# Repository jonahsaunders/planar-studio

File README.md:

# Planar Studio

Design planar inductors, transformers, PCB motors, filters and antennas inside
KiCad. Planar Studio reads your board's stack, calculates electrical estimates,
and places the generated copper into the PCB as one undoable operation.

**[Download v1.6.0](https://github.com/jonahsaunders/planar-studio/releases/download/v1.6.0/planar-studio-1.6.0.zip)**
· [Install](#install) · [Guides](#guides) · [Common PCB issues](docs/common-pcb-issues.md) · [Flyback example](#5-w-planar-flyback-example) · [GaN example](#60-w-gan-planar-llc-example) · [CoilTile example](#coiltile-usb-inductive-sensing-example)

## Explore the workspaces

Current application captures. Click a view to open the full-size image.

<table>
<tr>
<td width="50%" valign="top">
<h3>Inductors</h3>

<p>Shape windings, connect layers and route around obstacles.<br><a href="docs/winding-obstacles.md">Winding guide →</a></p>
</td>
<td width="50%" valign="top">
<h3>Transformers</h3>

<p>Build ferrite stacks, compare candidates and verify operating limits.<br><a href="docs/transformer-design.md">Transformer guide →</a></p>
</td>
</tr>
<tr>
<td width="50%" valign="top">
<h3>PCB motors</h3>

<p>Explore rotary, stepper, linear, dual-rotor and planar machines.<br><a href="docs/gallery.md#pcb-motors">See all five motor families →</a></p>
</td>
<td width="50%" valign="top">
<h3>Filters</h3>

<p>Turn LC and microstrip networks into copper and response plots.<br><a href="docs/engineering-models.md#filter-families">Filter models →</a></p>
</td>
</tr>
<tr>
<td width="50%" valign="top">
<h3>Antennas</h3>

<p>Design patches, arrays, directional radiators and NFC loops.<br><a href="docs/gallery.md#antennas">Explore antenna layouts →</a></p>
</td>
<td width="50%" valign="top">
<h3>Design tools</h3>

<p>Inspect fields, optimize geometry and compare measurements.<br><a href="docs/design-tools.md">Design tools guide →</a></p>
</td>
</tr>
</table>

**[Open the full 15-image gallery →](docs/gallery.md)** — obstacle routing,
transformer search, motor families, antenna variants and both interface themes.

Save editable designs, compare calculated responses, and export KiCad boards or
footprints, SVG, DXF, JSON and specification sheets. The **Design tools** panel
adds constrained searches, measurement overlays, tolerance studies and board
checks; see the [tools guide](docs/design-tools.md).

## Install

The **1.6.0 development release** supports KiCad **9.0.1 or newer** on Windows,
macOS and Linux. [Release notes](https://github.com/jonahsaunders/planar-studio/releases/tag/v1.6.0).

1. Download [planar-studio-1.6.0.zip](https://github.com/jonahsaunders/planar-studio/releases/download/v1.6.0/planar-studio-1.6.0.zip) and leave it zipped.
2. In KiCad's main Project Manager, open **Plugin and Content Manager**.
3. Choose **Install from File**, select the ZIP and apply pending changes.
4. Restart KiCad, open the PCB Editor, and launch **Planar Studio** after its
   Python environment finishes setting up.

<details>
<summary>Upgrading or getting a metadata error?</summary>

To upgrade, close Planar Studio and the PCB Editor. In **Plugin and Content
Manager → Installed**, uninstall the old version and apply pending changes
before installing the new ZIP. Saved designs are stored separately; preserve
the settings folder.

Use the installer linked above. GitHub's **Code → Download ZIP** and **Source
code** archives contain the repository, not a PCM installer.

</details>

## 5 W planar flyback example

A10 retains the winding-short repair, increases measured turn gaps to about 0.289 mm, enlarges T1 annular rings and removes tangent secondary-via contacts. Independent geometry, connection-width and full copper/mask Gerber checks protect these changes. Use the A10 package and the [common PCB issues reference](docs/common-pcb-issues.md) when reviewing or editing the design.

An **18–36 V DC to isolated 5 V / 1 A** converter with an LT8302 controller and
transformer windings built into a six-layer PCB. The example includes a KiCad 10
project, schematic, BOM, calculations and single-board manufacturing files for
JLCPCB-managed panelization.

**Unbuilt engineering prototype.** Factory acceptance and electrical, thermal
and magnetic qualification remain open.

[Explore the board and schematic](examples/planar-flyback-5w/README.md)
· [Review package](examples/PS-FLYBACK-5W-A10-review-package.zip)
· [Validation record](examples/planar-flyback-5w/VALIDATION.md)

## 60 W GaN planar LLC example

A **48 V nominal to isolated 12 V / 5 A target** using an integrated GaN half
bridge, silicon synchronous rectifiers and an eight-layer PCB transformer.
The 64 × 56 mm chamfered board has all electronics on top, removable screw-terminal ports,
and the flyback example's exposed-substrate M3 hole geometry on a 55 × 47 mm
pattern. The A10 schematic uses visible local wiring and has no four-way
connections. The accompanying MIT PER and video studies explain the layout decisions. An 82-reference ratings audit records the corrected parts and outstanding electrical limits.

**Unbuilt engineering prototype.** ERC, DRC, connectivity, assembly-file agreement
and a portable rebuild pass. Factory DFM, ferrite installation and electrical,
magnetic and thermal qualification remain open. 60 W is not a measured result.

**Manufacturing audit: do not order the current revision.** The five-board
review found overlapping same-net component lands, incomplete courtyards,
GaN stencil/mask and placement-origin issues, and a factory stack mismatch.
The [audit and cost breakdown](examples/planar-gan-60w/Manufacturing-audit.html)
record required corrections and unconfirmed turnkey operations.

[Explore the native KiCad example](examples/planar-gan-60w/README.md)
· [KiCad package](examples/PS-GAN-60W-A10-KiCad.zip)
· [Layout resource review](examples/planar-gan-60w/DEEP-LAYOUT-REVIEW.md)
· [PER design study](examples/planar-gan-60w/PER-DESIGN-STUDY.md)
· [Validation record](examples/planar-gan-60w/VALIDATION.md)

## CoilTile USB inductive sensing example

A **2 × 2 near-field metal-sensing array** using four printed coils generated by
Planar Studio, an LDC1614 converter and an MCP2221A USB bridge. The A3 schematic
shows one continuous USB → I²C → sensor → LC-tank signal path. The 72 × 90 mm
four-layer PCB reuses the flyback/GaN examples' exposed-substrate M3 edge holes.

Includes editable KiCad 9 files, a Python heatmap and CSV logger, an exact-code
JLCPCB BOM/CPL, Gerbers, and bring-up instructions. No firmware flashing is needed.
**Unbuilt prototype:** native ERC/DRC and connectivity checks pass; physical
sensing range, crosstalk and supplier assembly acceptance remain unverified.

[Explore CoilTile](examples/coil-tile/README.md)
· [Schematic PDF](examples/coil-tile/docs/CoilTile-schematic.pdf)
· [A3 review](examples/coil-tile/docs/A3-CHANGES.md)
· [Assembly handoff](examples/coil-tile/manufacturing/ORDER-NOTES.md)

## Guides

- [Design tools](docs/design-tools.md) — optimization, measurements, tolerances and board checks.
- [Layer setup and loaded transformers](docs/stack-load-antennas.md) — board layers, winding stacks and source/load models.
- [Directional antennas](docs/directional-antennas.md) — Vivaldi, Yagi, log-periodic and bow-tie layouts.
- [Engineering models](docs/engineering-models.md) — equations, reference comparisons, assumptions and limits.
- [Development](docs/development.md) — run without KiCad, build an installer, run checks and capture screenshots.

Calculated performance depends on the selected model. Review its assumptions
and validate the resulting hardware with appropriate simulation, KiCad DRC and
measurements. Transformer loss or thermal results that cannot be calculated are
reported as unknown.

Built on [planar-coil-studio](https://github.com/jonahsaunders/planar-coil-studio).
Released under the [MIT license](LICENSE).

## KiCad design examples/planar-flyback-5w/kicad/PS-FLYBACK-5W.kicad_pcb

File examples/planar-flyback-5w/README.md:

# PS-FLYBACK-5W A10 — winding clearance repairs

An engineering prototype for 18–36 V input and isolated 5 V / 1 A output. [Review report](report.html) · [Validation](VALIDATION.md) · [Manufacturing handoff](manufacturing/START-HERE.md).

**A10 retains the winding-short repair and adds clearance margin.** A7's wide SW landing shorted part of the primary. A8 repaired that landing but retained turn gaps of about 0.191 mm against a 0.200 mm rule. A9 measured approximately 0.240 mm. A10 uses 0.30 mm nominal spacing and measures approximately **0.289 mm** between turns on all four winding layers. The winding stays 0.6 mm wide with 4:2 turns. T1 terminals and attached approaches are updated; both SW necks are retained, and the SEC_A landing retains its 1 mm neck to preserve core-edge clearance. [Repair history](WINDING-CLEARANCE-REVISION.md).

**[Common PCB issues and checks](COMMON-ISSUES.md)** records the causes, why DRC missed them, and how to prevent recurrence. The schematic and PCB drawing layer point to this reference. Independent checks cover external copper, internal turn spacing, physical current paths and matching Gerber winding regions. Regression tests reject the original spacing defect and added/missing copper. [Spacing evidence](evidence/audit/winding-integrity-checks.json) · [A9-to-A10 comparison](evidence/audit/a10-revision-checks.json).

Four secondary via lands increase from 0.90 to 1.00 mm to eliminate tangent contacts. T1 lands increase from 0.60 to 0.70 mm around unchanged 0.30 mm holes, providing 0.20 mm annular rings. The winding size setting increases from 13.6 to 13.9 mm to preserve core-slot clearance. A10 retains the circuit values, component placements, OSP finish, 649 kΩ R1 / C25821, 180 Ω R7, core pair and stack. Resistance, leakage and capacitance estimates are refreshed from the revised winding paths. The estimated magnetizing inductance remains 13.12 µH. Earlier procurement stock figures are historical snapshots. [R1 procurement](PROCUREMENT-REVISION.md) · [Preload derivation](PRELOAD-REVISION.md).

The retained 39 Ω / 2 W snubber screens at **0.638 W**. Its repetitive-pulse capability and measured clamp/thermal behavior remain unqualified. [Snubber review](SNUBBER-REVIEW.md).

## 3D assembly

KiCad render of the saved A10 board. [Underside view](evidence/audit/board-3d-underside.png) · [Side view](evidence/audit/board-3d-side.png) · [STEP model](3d/PS-FLYBACK-5W.step) · [GLB model](3d/PS-FLYBACK-5W.glb). Package/core geometry is nominal; mounting hardware and clip retention include provisional envelopes. See [3D model sources and scope](3D-MODELS.md).

## Layer stack

The cross-section uses the published reference in [stackup.json](stackup.json): **1.609 mm excluding solder mask**, ordered as **1.6 mm nominal**. Layer heights in the illustration are not to scale. This is a modeling reference; the delivered factory construction still needs confirmation.

### Individual copper layers

Each image shows one exported Gerber layer in the same top-view orientation and at the same scale. Read left to right, then down, from L1 to L6; click any image for the full resolution.

| L1 · F.Cu — top | L2 · In1.Cu | L3 · In2.Cu |
| --- | --- | --- |
|  |  |  |
| **L4 · In3.Cu** | **L5 · In4.Cu** | **L6 · B.Cu — bottom** |
|  |  |  |

The primary connects the two-turn windings on **F.Cu and B.Cu in series** for four turns. The two-turn secondary windings on **In1.Cu and In4.Cu connect in parallel**. In2.Cu and In3.Cu carry routing and via pads, with no transformer winding. [Mask, paste, silkscreen and outline views](evidence/audit/gerber-technical-overview.png).

## Schematic

Current A10 schematic exported from KiCad. Open the image to zoom, or download the [native schematic](kicad/PS-FLYBACK-5W.kicad_sch).

## Retained construction

The board is 44 × 94 mm with a 35 × 85 mm mounting pattern and 10 mm copper exclusions around the M3 holes on all six layers. Order nominal 1.6 mm, 1 oz outer / 1 oz inner copper, Specify Stackup: No, OSP finish, and Standard PCBA. The model retains the published default 1.609 mm reference construction; the delivered stack still needs confirmation. [Stack background](STACK-REVISION.md).

The 4:2 planar transformer uses two factory-gapped TDK B66285G0050X187 N87 ELP22 halves and two B66286A2000X000 spring clips. No grinding or adhesive is specified. Install the core pair after PCBA and measure assembled inductance. All 29 footprints have local visible models. [Core installation](manufacturing/CORE-ASSEMBLY.md) · [3D sources](3D-MODELS.md).

## Checks and remaining work

Native ERC/DRC, schematic parity, package/net mapping, winding-spacing and terminal-change containment, mounting/clip clearance, solid fit and manufacturing export checks are recorded in VALIDATION.md. Standard silkscreen text is at least 1.0 mm high with 0.15 mm strokes and a 0.15 mm clearance rule.

The placement check covers 24 components, 50 saved exact-part catalog pad centers, four R1/R6 manufacturer land centers and two R7 same-series reference centers, with 15 rejected incorrect rotations/origins. Replacement R1/R6/R7 catalog geometry was unavailable; confirm these centered nonpolar placements in the fresh factory preview. [Placement review](manufacturing/PLACEMENT-REVIEW.md).

This remains an unbuilt prototype. Supplier acceptance of the stack, filled/capped vias, panel, Standard-PCBA reflow and connector process is open. Bench qualification must establish clamp and RFB waveforms, snubber pulse/thermal behavior, regulation, magnetics, startup/fault behavior and clip retention. The A10 repair has been checked in CAD; hardware qualification remains open.

## Rebuild

Run `scripts/rebuild.py --kicad-cli <KiCad-10-cli> --kicad-python <KiCad-Python-or-wrapper> --cadquery-python <Python-with-CadQuery-PyGerber-Pillow> --geometry-python <Python-with-Shapely-2.2-and-PyGerber-2.4.3>`. If Shapely is available in the CadQuery environment, omit `--geometry-python`. Node and Sharp rasterize the schematic; use `--node` and `--sharp-module` when they are not on the default paths. The default uses the saved A10 winding/core source; `--regenerate-magnetics` regenerates it from the repository engine and `winding-clearance.json`. The A10 comparison bounds winding, terminal, approach and four via-land changes. Nonzero connection-width, mask-clearance and annular-ring checks run alongside independent winding and complete copper/mask Gerber comparisons. The build refreshes native files, checks, manufacturing data, views and the A10 review ZIP.

The current A10 evidence is enumerated in VALIDATION.md. Earlier A1–A9 reports and images are historical context, not fresh proof for this board.

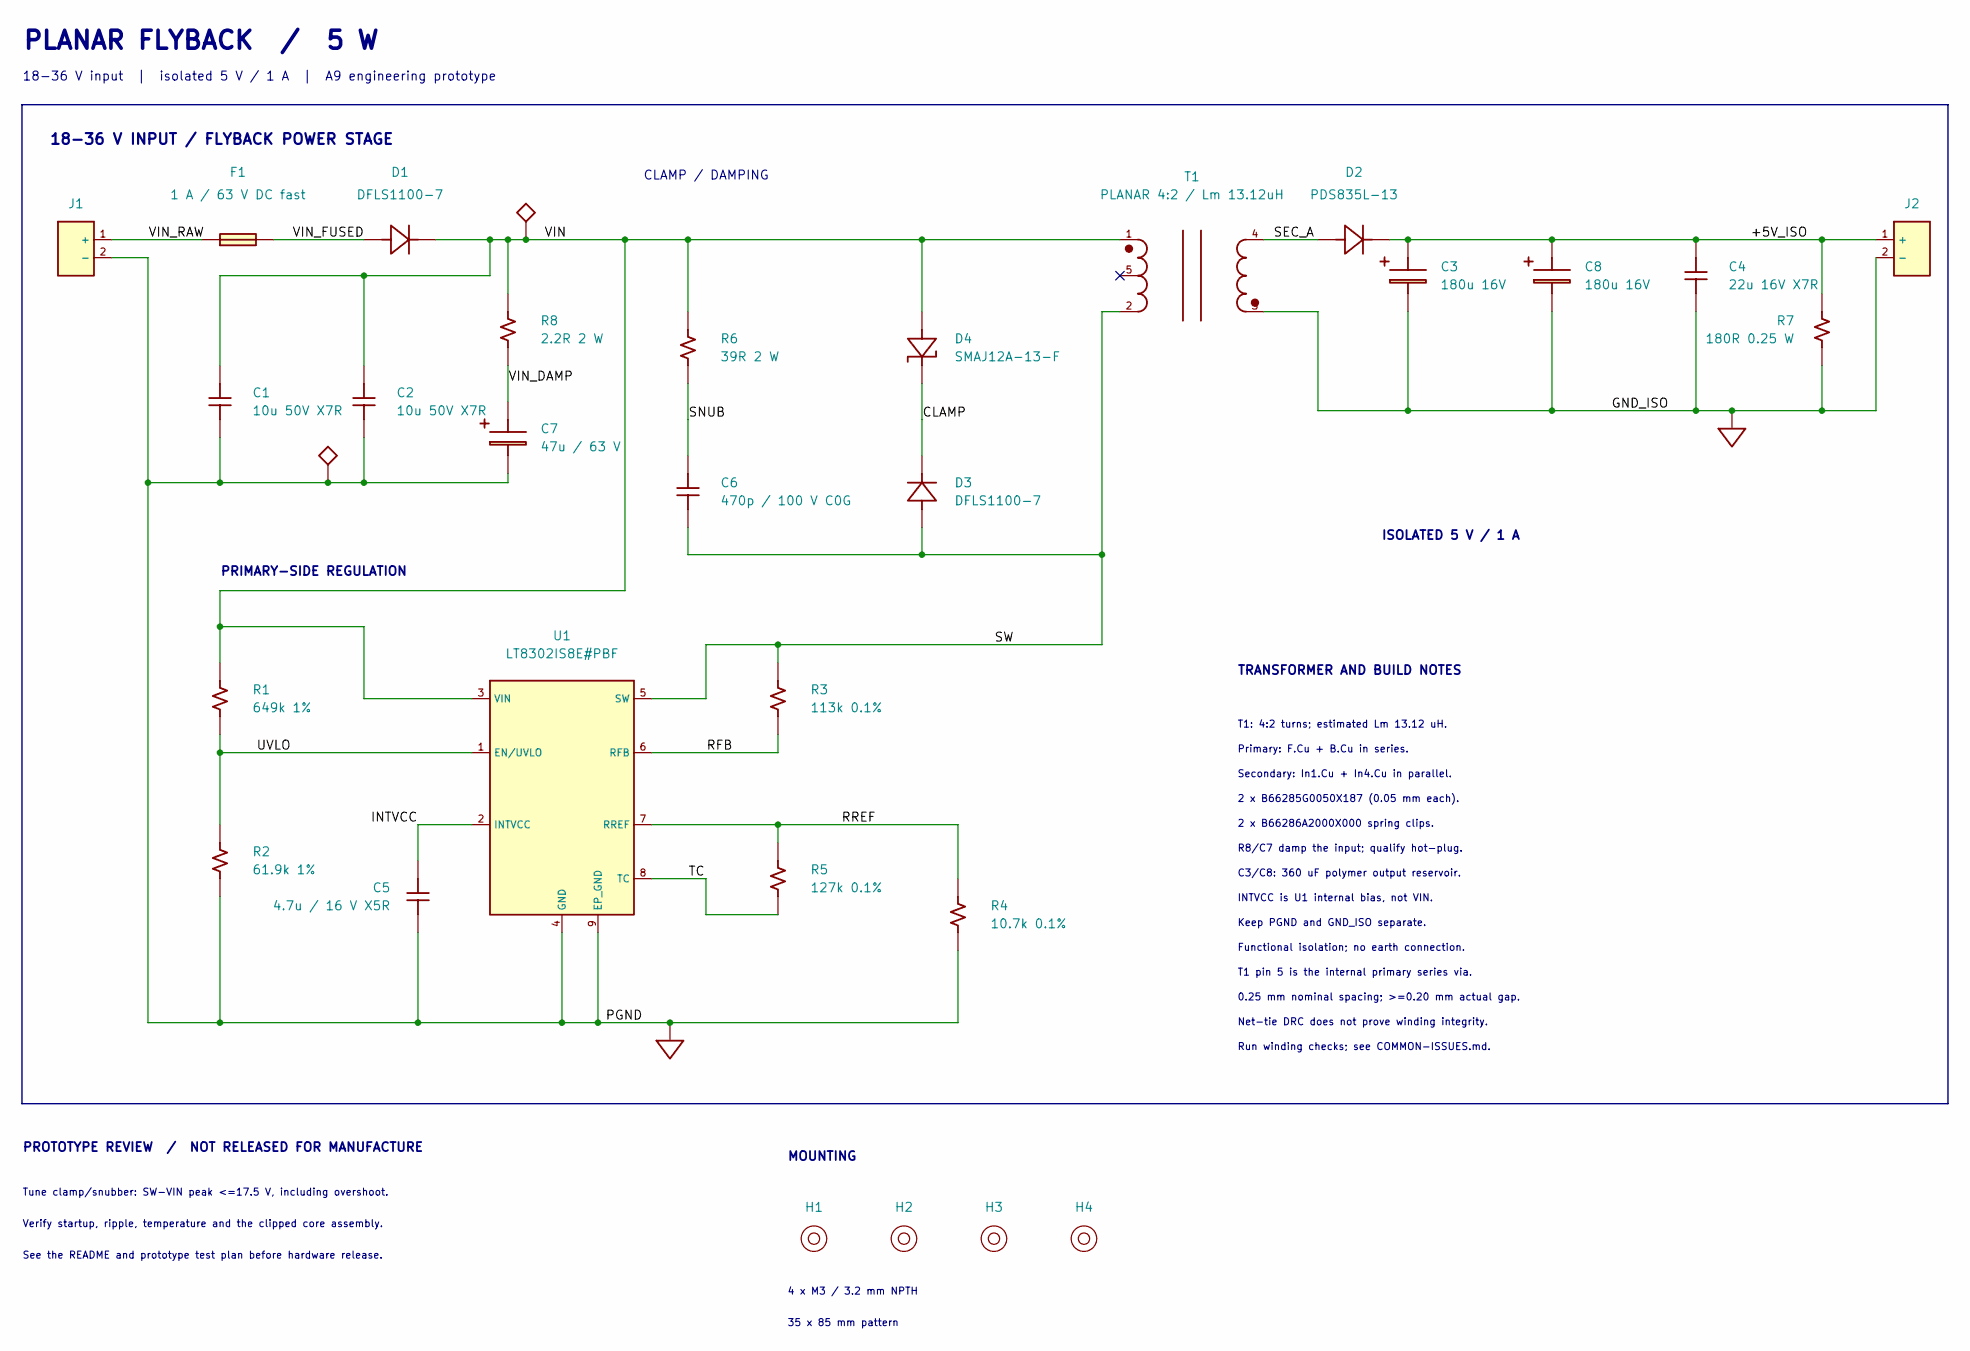
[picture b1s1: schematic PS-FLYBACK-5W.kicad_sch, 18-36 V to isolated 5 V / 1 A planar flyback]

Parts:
C1, C2: 10u 50V X7R; C_1210_3225Metric; MPN CL32B106KBJNNNE; LCSC C138687
C3, C8: 180u 16V; CP_Panasonic_C6; MPN 16SVPF180M; LCSC C136277
C4: 22u 16V X7R; C_1210_3225Metric; MPN CL32B226KOJNNNE; LCSC C55530
C5: 4.7u / 16 V X5R; C_0603_1608Metric; MPN GRM188R61C475KE11D; LCSC C77045
C6: 470p / 100 V C0G; C_0805_2012Metric; MPN CC0805JRNPO0BN471; LCSC C513677
C7: 47u / 63 V; CP_Elec_8x10.5; MPN EEHZC1J470P; LCSC C454353
D1, D3: DFLS1100-7; D_PowerDI-123; MPN DFLS1100-7; LCSC C107674
D2: PDS835L-13; D_PowerDI-5; MPN PDS835L-13; LCSC C444972
D4: SMAJ12A-13-F; D_SMA; MPN SMAJ12A-13-F; LCSC C134947
F1: 1 A / 63 V DC fast; Fuse_Bourns_SF1206F; MPN SF-1206F100-2; LCSC C3164649
H1, H2, H3, H4: M3 / 3.2 mm NPTH; MountingHole_3.2mm_M3_ExposedSubstrate_Edge
J1: 18-36 V DC; Terminal_KF301_2P_5.00; MPN KF301-5.0-2P; LCSC C474881
J2: 5 V / 1 A isolated; Terminal_KF301_2P_5.00; MPN KF301-5.0-2P; LCSC C474881
R1: 649k 1%; R_0603_1608Metric; MPN 0603WAF6493T5E; LCSC C25821
R2: 61.9k 1%; R_0603_1608Metric; MPN RC0603FR-0761K9L; LCSC C137696
R3: 113k 0.1%; R_0603_1608Metric; MPN RT0603BRD07113KL; LCSC C705718
R4: 10.7k 0.1%; R_0603_1608Metric; MPN RT0603BRD0710K7L; LCSC C861078
R5: 127k 0.1%; R_0603_1608Metric; MPN RT0603BRD07127KL; LCSC C705722
R6: 39R 2 W; R_EverOhms_CRH2512; MPN CRH2512F39R0E04Z; LCSC C175263
R7: 180R 0.25 W; R_1206_3216Metric; MPN RC1206FR-07180RL; LCSC C137380
R8: 2.2R 2 W; R_Bourns_CRM2512; MPN CRM2512-JW-2R2ELF; LCSC C840598
T1: PLANAR 4:2 / Lm 13.12uH; Planar_EELP22_4T_2T; MPN PS-MAG-002 A2
U1: LT8302IS8E#PBF; SOIC8_EP_LT_S8E; MPN LT8302IS8E#PBF; LCSC C673679

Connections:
/+5V_ISO: C3.1, C4.1, C8.1, D2.1 (K), J2.1 (+), R7.1
/CLAMP: D3.1 (K), D4.1 (K)
/GND_ISO: C3.2, C4.2, C8.2, J2.2 (-), R7.2, T1.3 (S_DOT)
/INTVCC: C5.1, U1.2 (INTVCC)
/PGND: C1.2, C2.2, C5.2, C7.2, J1.2 (-), R2.2, R4.2, U1.4 (GND), U1.9 (EP_GND)
/RFB: R3.2, U1.6 (RFB)
/RREF: R4.1, R5.2, U1.7 (RREF)
/SEC_A: D2.2 (A), T1.4 (S_END)
/SNUB: C6.1, R6.2
/SW: C6.2, D3.2 (A), R3.1, T1.2 (P_END), U1.5 (SW)
/TC: R5.1, U1.8 (TC)
/UVLO: R1.2, R2.1, U1.1 (EN/UVLO)
/VIN: C1.1, C2.1, D1.1 (K), D4.2 (A), R1.1, R6.1, R8.1, T1.1 (P_DOT), U1.3 (VIN)
/VIN_DAMP: C7.1, R8.2
/VIN_FUSED: D1.2 (A), F1.2
/VIN_RAW: F1.1, J1.1 (+)

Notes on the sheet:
PRIMARY-SIDE REGULATION
CLAMP / DAMPING
ISOLATED 5 V / 1 A
TRANSFORMER AND BUILD NOTES
T1: 4:2 turns; estimated Lm 13.12 uH.
Primary: F.Cu + B.Cu in series.
Secondary: In1.Cu + In4.Cu in parallel.
2 x B66285G0050X187 (0.05 mm each).
2 x B66286A2000X000 spring clips.
R8/C7 damp the input; qualify hot-plug.
C3/C8: 360 uF polymer output reservoir.
INTVCC is U1 internal bias, not VIN.
Keep PGND and GND_ISO separate.
Functional isolation; no earth connection.
T1 pin 5 is the internal primary series via.
0.25 mm nominal spacing; >=0.20 mm actual gap.
Net-tie DRC does not prove winding integrity.
Run winding checks; see COMMON-ISSUES.md.
PLANAR FLYBACK / 5 W
18-36 V input | isolated 5 V / 1 A | A9 engineering prototype
18-36 V INPUT / FLYBACK POWER STAGE
PROTOTYPE REVIEW / NOT RELEASED FOR MANUFACTURE
Tune clamp/snubber: SW-VIN peak <=17.5 V, including overshoot.
Verify startup, ripple, temperature and the clipped core assembly.
See the README and prototype test plan before hardware release.
MOUNTING
4 x M3 / 3.2 mm NPTH
35 x 85 mm pattern

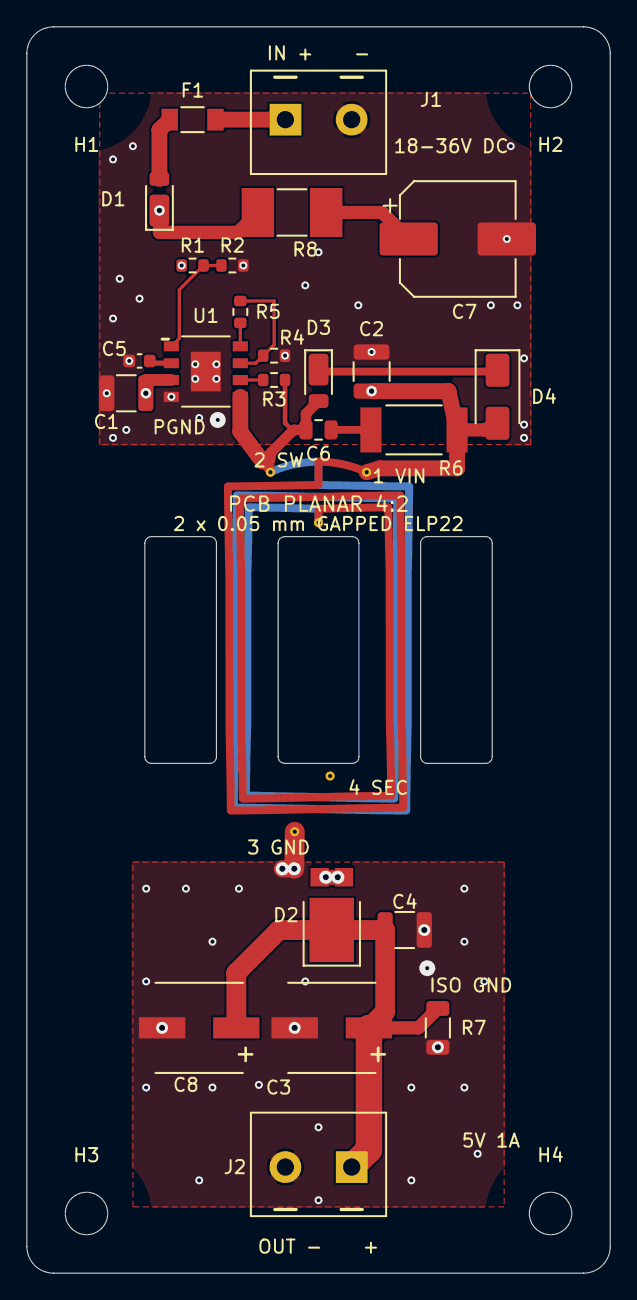
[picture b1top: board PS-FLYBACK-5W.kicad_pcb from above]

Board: 6 copper layers, 44.0 x 94.0 mm, 29 parts (0 on the bottom side), 16 nets.

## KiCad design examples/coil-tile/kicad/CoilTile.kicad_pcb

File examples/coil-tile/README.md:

# CoilTile A3 — a four-pixel metal-sensing PCB

**Prototype design, not yet fabricated or tested on hardware.** Four printed
24 mm coils sense changes in nearby conductive targets. An LDC1614 measures
their resonant frequencies; an MCP2221A connects them to a USB desktop heatmap.
This is a near-field inductive array, not radar or an RF direction-finding array.

A3 keeps the continuous USB-C → ESD → USB/I²C bridge → sensor → LC-tank
schematic, with smaller symbols, tighter spacing and clear service notes.
The PCB has shorter I²C/CC1 routes, labeled service pads and a closer sensor
bypass capacitor. All four mounting holes retain the American Embedded
exposed-substrate footprint used by the flyback and GaN examples.
See [A3 changes and measured routing improvements](docs/A3-CHANGES.md).

[View the schematic PDF](docs/CoilTile-schematic.pdf) · [Angled 3D view](evidence/assembled-board-perspective.png) · [3D model details](docs/3D-MODELS.md).

## What is included

| Folder | Contents |
|---|---|
| `kicad/` | Editable KiCad 9 project, schematic, routed PCB, local symbols and footprints |
| `docs/CoilTile-schematic.pdf` | Readable one-sheet A3 schematic |
| `manufacturing/` | Fabrication ZIP, JLCPCB BOM and placement CSV, order notes |
| `software/` | USB driver, 2×2 heatmap, baseline calibration, CSV logger, explicit demo mode |
| `planar-studio/` | Coil configuration, generated artwork, geometry and estimated model |
| `evidence/` | Native ERC/DRC, netlist, layer/Gerber previews, assembly checks and software tests |
| `scripts/` | Source generators and release/export checks |

Start by opening `kicad/CoilTile.kicad_pro`, then read `docs/BRINGUP.md` and
`manufacturing/ORDER-NOTES.md`. The board is fully routed. There is no firmware
image or programming service to arrange: MCP2221A uses factory USB firmware.
The Python application runs on the computer, not the PCB.

## Design

72 × 90 mm, 1.6 mm FR-4, four copper layers, 20 assembled components on the top.
Four 3.2 mm mounting holes have 6.4 mm exposed-substrate mask openings and 10 mm
copper exclusion circles, with mask extensions toward the nearest side edge.
They retain the 64 × 82 mm mounting pattern and take nylon hardware. The analog converter sits at the
center; USB, ESD protection and a 3.3 V linear regulator occupy the bottom strip.

The four single-layer coils use 16 turns of 0.20 mm trace / 0.20 mm spacing.
Planar Studio estimates about 5.51 µH per coil. A 220 pF C0G capacitor gives an
ideal resonance near 4.57 MHz; routing, materials, targets and mutual coupling
will shift that. Inner coil terminals return on the back. Ground and power
planes are kept outside the sensing disks. Coils remain covered by soldermask.

Four layers were chosen for dependable power and return paths around the USB
bridge and sensor. This costs more bare-board area than two layers, but avoids
a fragile two-layer escape layout. The board uses standard through vias and
no via-in-pad fabrication, blind vias, or solder-mask-defined fine-pitch tricks.

The heatmap shows relative frequency changes. It does not claim distance,
material identity, four independent spatial pixels, or a validated detection
range. Start experiments with coins/washers a few millimeters away. Backside
metal also affects it. Use a plastic stand and keep a laptop chassis away.

## Cost and assembly

Planning allowance: **roughly US$85–120 for five assembled boards before
shipping/tax**, not a JLCPCB quotation. The two main ICs account for most of the
parts cost. Small-order setup, extended-component fees, stencil, QFN inspection,
connector soldering and wastage can outweigh the bare PCB price. Actual service
eligibility, stock and all fees must be checked in JLCPCB's order review.

All purchased parts have exact LCSC codes in the native schematic and BOM.
The coils, test pads and mounting holes are fabricated features, not BOM parts.
Request complete top-side assembly including the USB connector's shell stakes.
No order has been placed. A cable and nylon standoffs are not included in the BOM.

## Verification and remaining work

KiCad 9.0.9 ERC and DRC report **zero violations**, zero unrouted connections,
and zero schematic parity issues. BOM and CPL both contain exactly the same
20 assembly references. Gerber copper/mask/paste/silk/outline files were parsed
and rendered separately from the native PCB. Schematic PDF and layer views
were visually reviewed. Seven mocked driver tests pass; headless demo/CSV runs.

These checks cannot verify oscillation amplitude, USB signal integrity, sensor
noise, usable range, crosstalk or assembly yield. The first batch is for bring-up
and characterization. The GUI/USB path still needs a real-machine/device run.
See `docs/VALIDATION.md` for the exact boundaries of the verification.

## References used

Built using the [KiStack](https://github.com/American-Embedded/kistack) schematic,
PCB, BOM and export workflows, and
[Planar Studio](https://github.com/jonahsaunders/planar-studio)'s actual inductor
engine. Reviewed its planar-flyback example generators, schematic and layout
audits for portable libraries, winding artwork/net-tie handling, readable
schematics and release checks. Those examples are not proof this sensor works.

Commit pins, datasheet links, licenses and design choices are in
`docs/REFERENCES.md`. See `docs/REBUILD.md` before running the generators: they
overwrite the native design files, so edit in KiCad or regenerate deliberately.

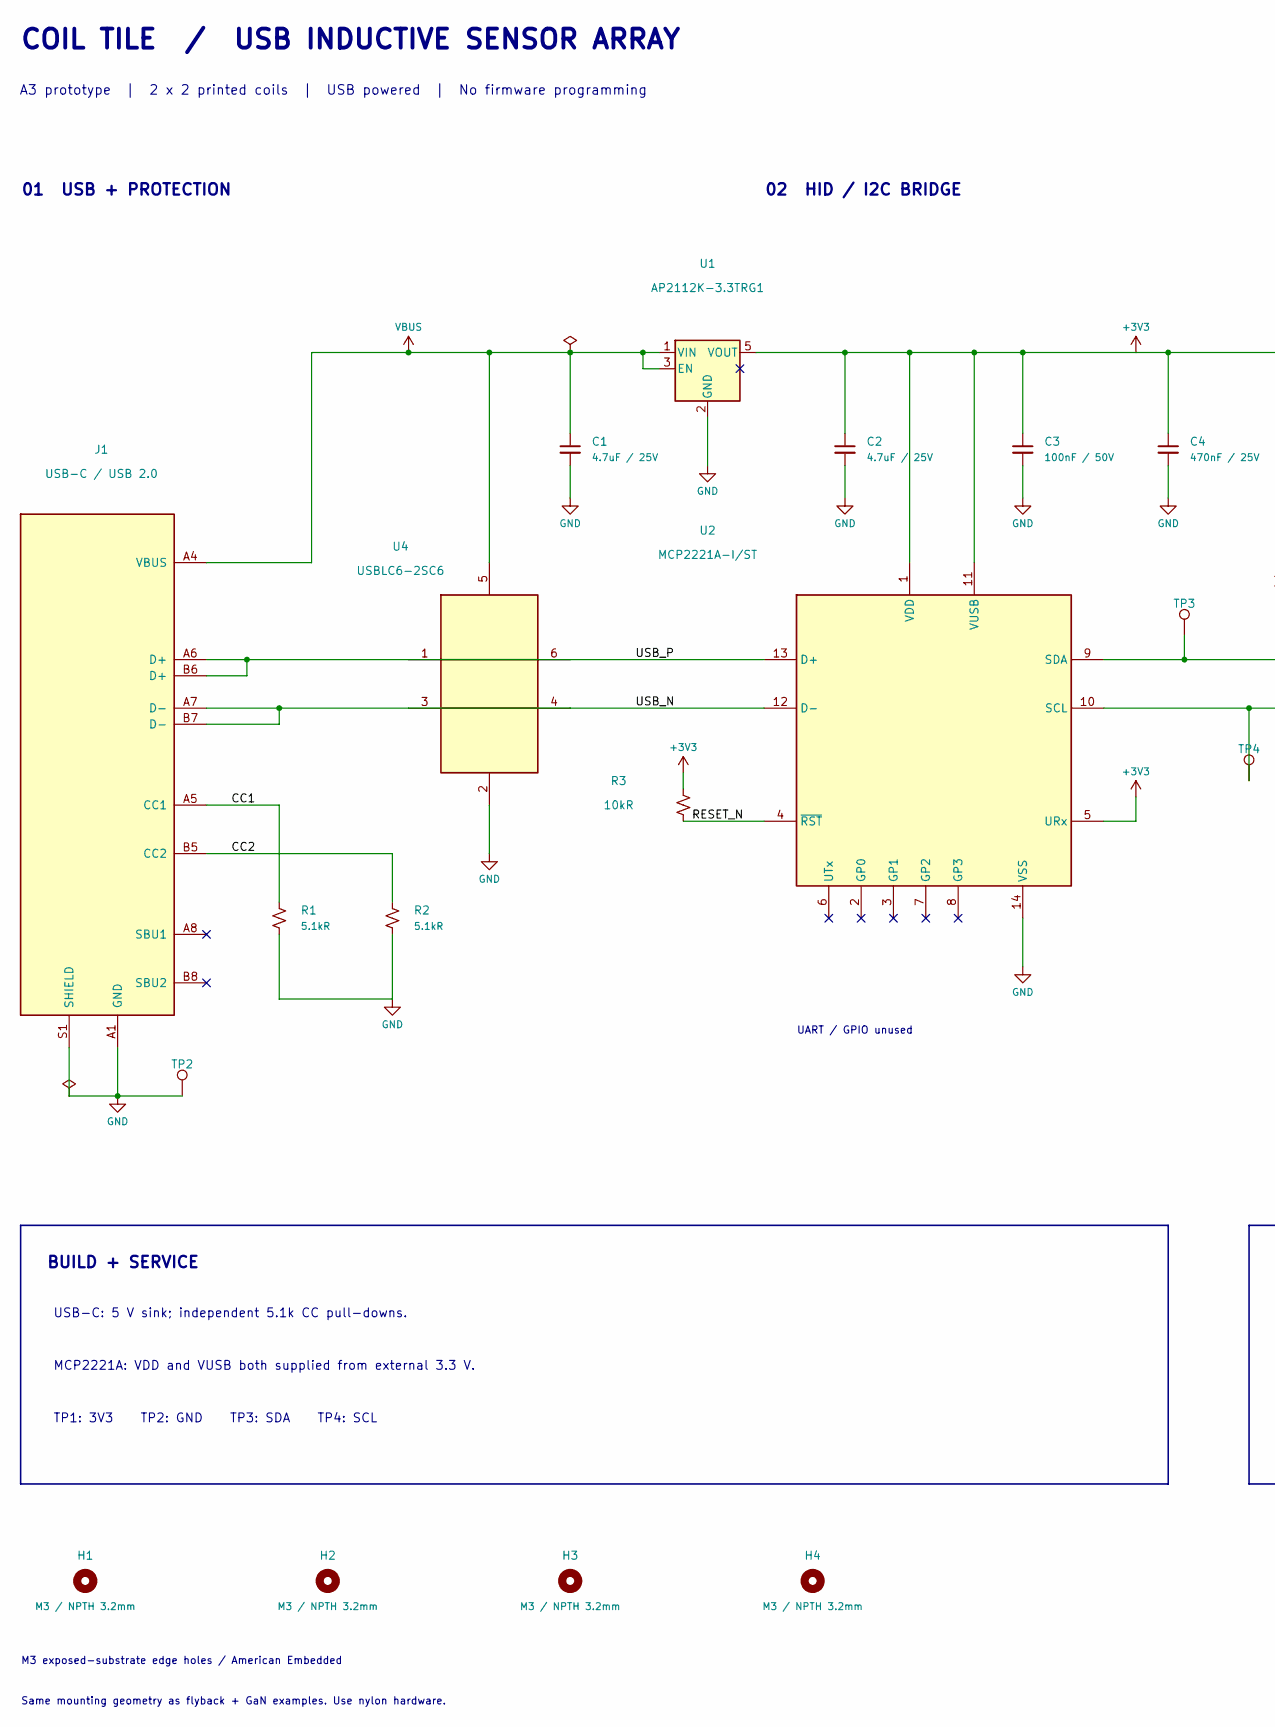
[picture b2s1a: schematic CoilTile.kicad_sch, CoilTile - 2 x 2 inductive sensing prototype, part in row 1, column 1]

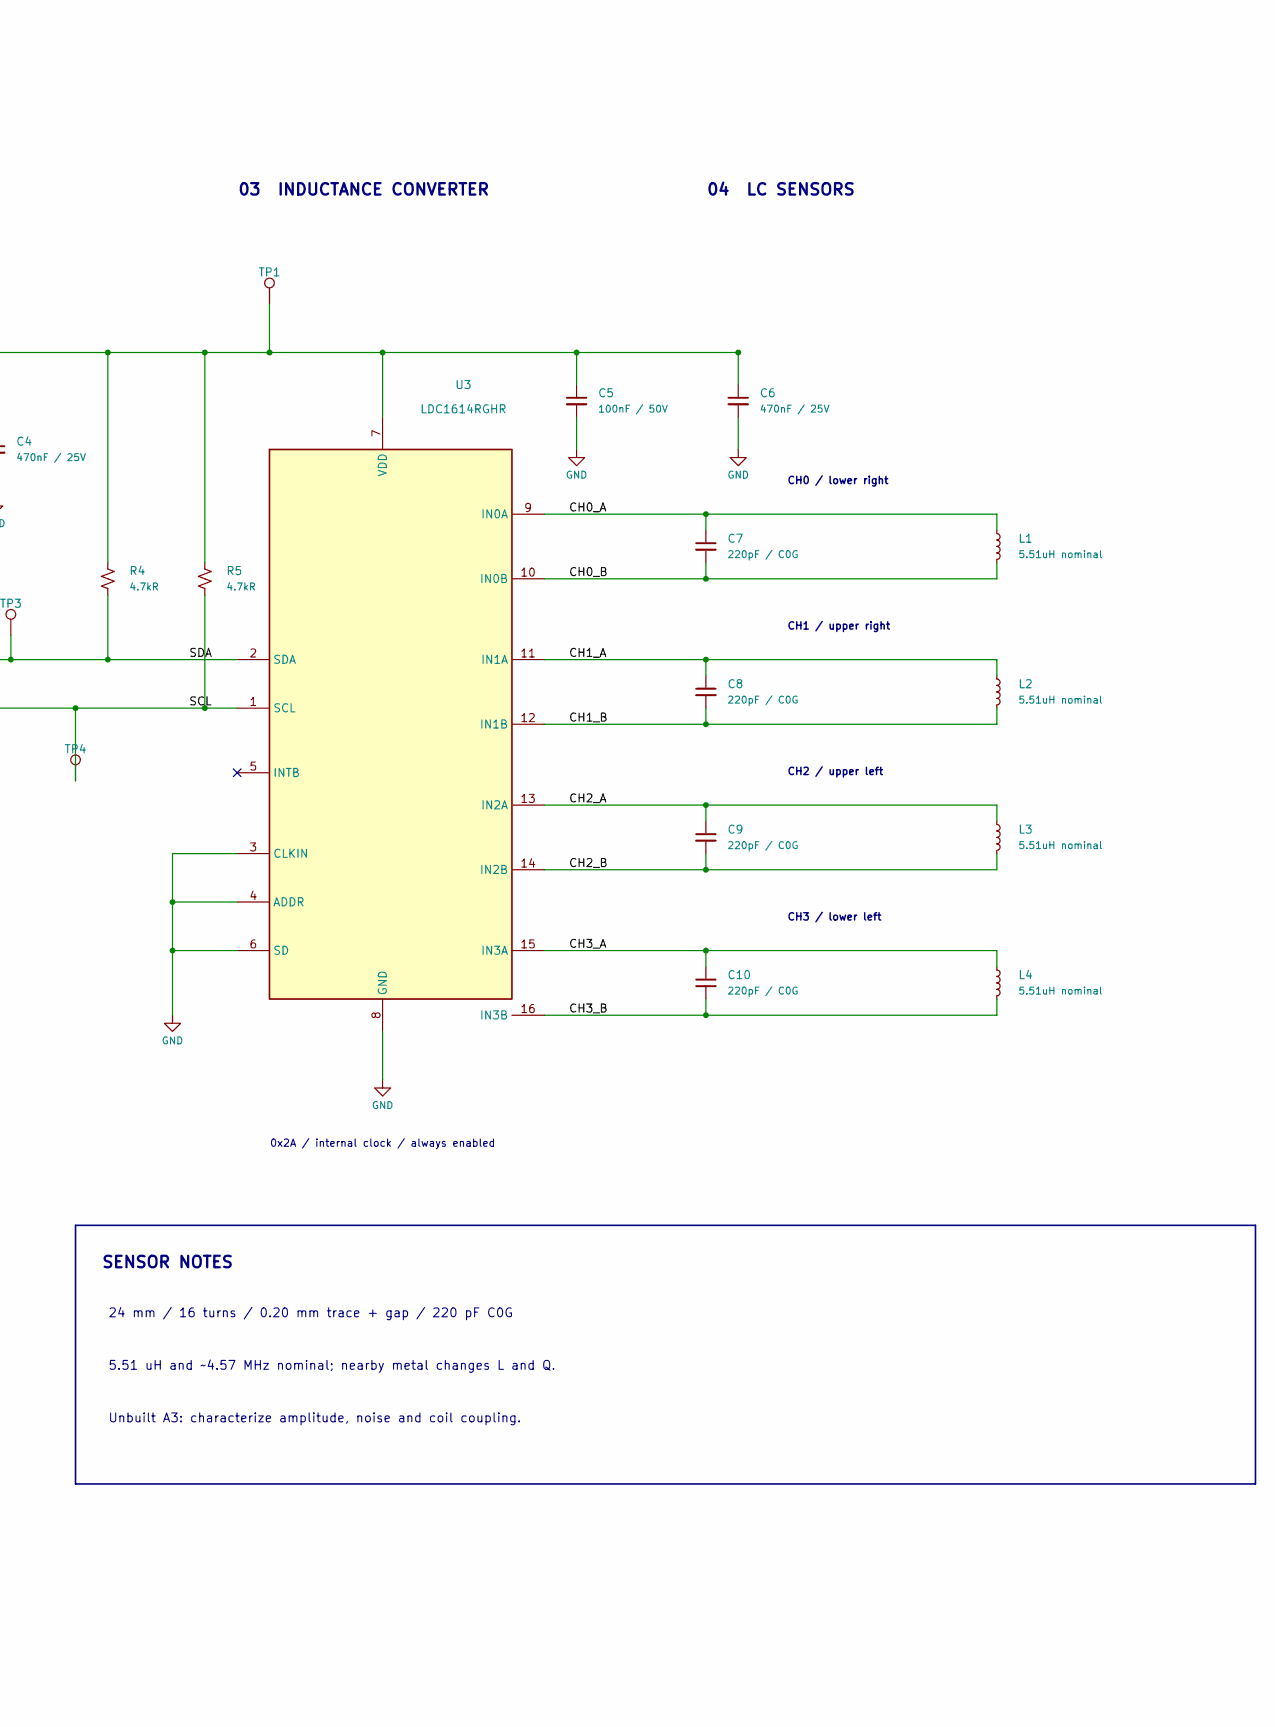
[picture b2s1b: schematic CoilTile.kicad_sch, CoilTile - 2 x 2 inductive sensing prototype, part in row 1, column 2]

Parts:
C1, C2: 4.7uF / 25V; C_0805_2012Metric; MPN CC0805KKX7R8BB475; LCSC C354262
C3, C5: 100nF / 50V; C_0603_1608Metric; MPN CC0603KRX7R9BB104; LCSC C14663
C4, C6: 470nF / 25V; C_0603_1608Metric; MPN CL10B474KA8NNNC; LCSC C1623
C7, C8, C9, C10: 220pF / C0G; C_0603_1608Metric; MPN 0603CG221J500NT; LCSC C156398
H1, H2, H3, H4: M3 / NPTH 3.2mm; MountingHole_3.2mm_M3_ExposedSubstrate_Edge
J1: USB-C / USB 2.0; USB_C_Receptacle_HRO_TYPE-C-31-M-12; MPN TYPE-C-31-M-12; LCSC C165948
L1, L2, L3, L4: 5.51uH nominal; Planar_24mm_16T; MPN PCB winding / not fitted
R1, R2: 5.1kR; R_0603_1608Metric; MPN 0603WAF5101T5E; LCSC C23186
R3: 10kR; R_0603_1608Metric; MPN 0603WAF1002T5E; LCSC C25804
R4, R5: 4.7kR; R_0603_1608Metric; MPN 0603WAF4701T5E; LCSC C23162
TP1: +3V3; TestPoint_Pad_D1.0mm
TP2: GND; TestPoint_Pad_D1.0mm
TP3: SDA; TestPoint_Pad_D1.0mm
TP4: SCL; TestPoint_Pad_D1.0mm
U1: AP2112K-3.3TRG1; SOT-23-5; MPN AP2112K-3.3TRG1; LCSC C51118
U2: MCP2221A-I/ST; TSSOP-14_4.4x5mm_P0.65mm; MPN MCP2221A-I/ST; LCSC C130462
U3: LDC1614RGHR; WQFN-16-1EP_4x4mm_P0.5mm_EP2.6x2.6mm; MPN LDC1614RGHR; LCSC C968448
U4: USBLC6-2SC6; SOT-23-6; MPN USBLC6-2SC6; LCSC C7519

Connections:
+3V3: C2.1, C3.1, C4.1, C5.1, C6.1, R3.1, R4.1, R5.1, TP1.1, U1.5 (VOUT), U2.1 (VDD), U2.5 (URx), U2.11 (VUSB), U3.7 (VDD)
/CC1: J1.A5 (CC1), R1.1
/CC2: J1.B5 (CC2), R2.1
/CH0_A: C7.1, L1.1, U3.9 (IN0A)
/CH0_B: C7.2, L1.2, U3.10 (IN0B)
/CH1_A: C8.1, L2.1, U3.11 (IN1A)
/CH1_B: C8.2, L2.2, U3.12 (IN1B)
/CH2_A: C9.1, L3.1, U3.13 (IN2A)
/CH2_B: C9.2, L3.2, U3.14 (IN2B)
/CH3_A: C10.1, L4.1, U3.15 (IN3A)
/CH3_B: C10.2, L4.2, U3.16 (IN3B)
/RESET_N: R3.2, U2.4 (~RST)
/SCL: R5.2, TP4.1, U2.10 (SCL), U3.1 (SCL)
/SDA: R4.2, TP3.1, U2.9 (SDA), U3.2 (SDA)
/USB_N: J1.A7 (D-), J1.B7 (D-), U2.12 (D-), U4.3 (I/O2), U4.4 (I/O2)
/USB_P: J1.A6 (D+), J1.B6 (D+), U2.13 (D+), U4.1 (I/O1), U4.6 (I/O1)
GND: C1.2, C2.2, C3.2, C4.2, C5.2, C6.2, J1.A1 (GND), J1.A12 (GND), J1.B1 (GND), J1.B12 (GND), J1.S1 (SHIELD), R1.2, R2.2, TP2.1, U1.2 (GND), U2.14 (VSS), U3.3 (CLKIN), U3.4 (ADDR), U3.6 (SD), U3.8 (GND), U3.17 (GND), U4.2 (GND)
VBUS: C1.1, J1.A4 (VBUS), J1.A9 (VBUS), J1.B4 (VBUS), J1.B9 (VBUS), U1.1 (VIN), U1.3 (EN), U4.5 (VBUS)

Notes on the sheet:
COIL TILE / USB INDUCTIVE SENSOR ARRAY
A3 prototype | 2 x 2 printed coils | USB powered | No firmware programming
01 USB + PROTECTION
02 HID / I2C BRIDGE
03 INDUCTANCE CONVERTER
04 LC SENSORS
UART / GPIO unused
0x2A / internal clock / always enabled
CH0 / lower right
CH1 / upper right
CH2 / upper left
CH3 / lower left
BUILD + SERVICE
USB-C: 5 V sink; independent 5.1k CC pull-downs.
MCP2221A: VDD and VUSB both supplied from external 3.3 V.
TP1: 3V3 TP2: GND TP3: SDA TP4: SCL
SENSOR NOTES
24 mm / 16 turns / 0.20 mm trace + gap / 220 pF C0G
5.51 uH and ~4.57 MHz nominal; nearby metal changes L and Q.
Unbuilt A3: characterize amplitude, noise and coil coupling.
M3 exposed-substrate edge holes / American Embedded
Same mounting geometry as flyback + GaN examples. Use nylon hardware.

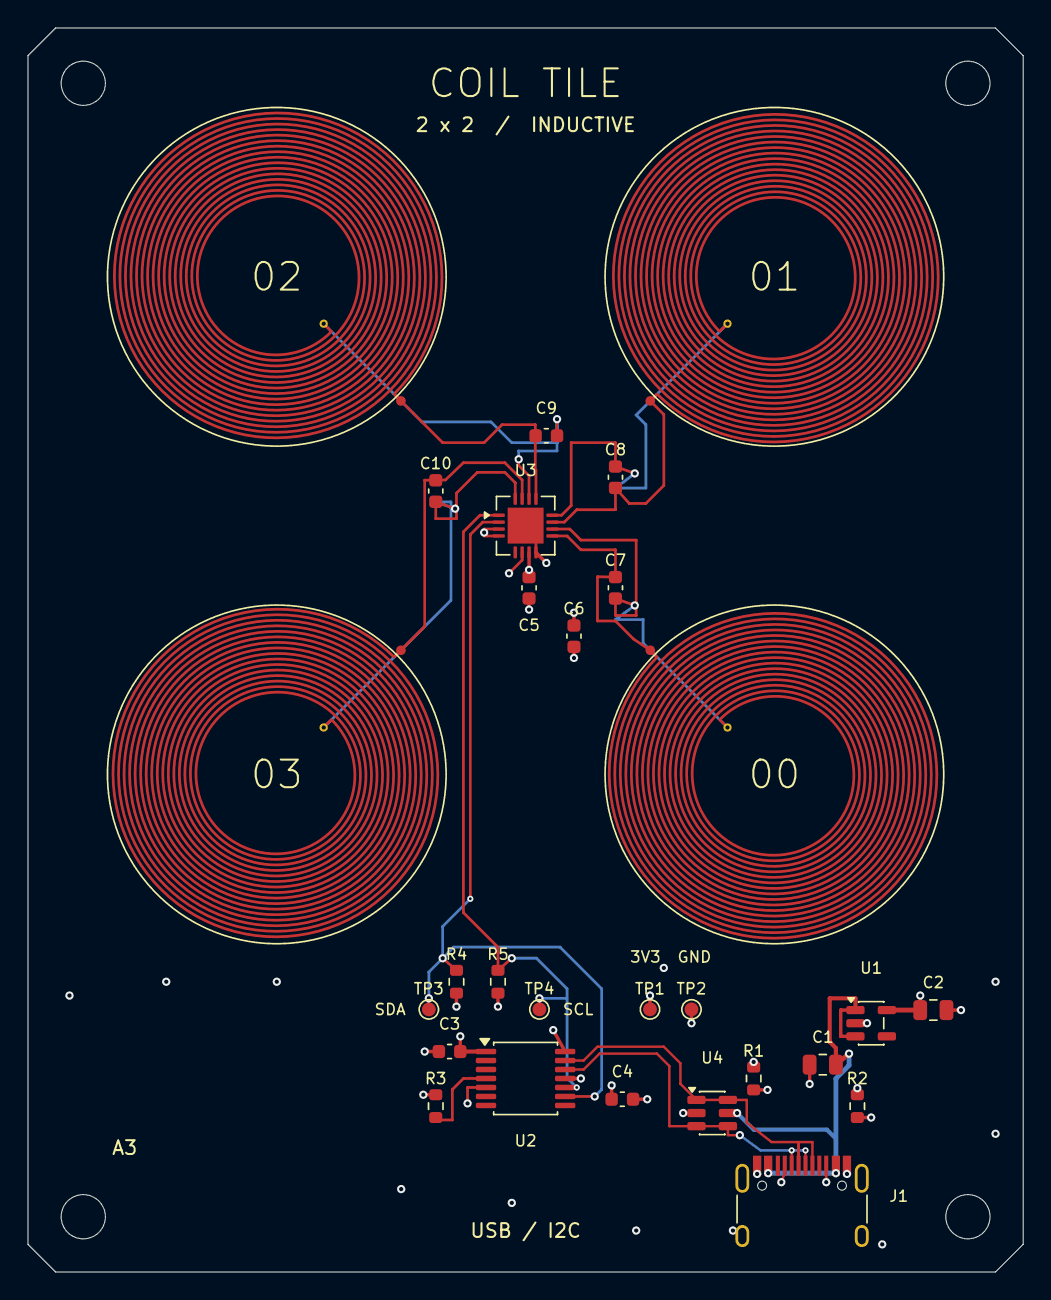
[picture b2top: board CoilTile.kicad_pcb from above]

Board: 4 copper layers, 72.0 x 90.0 mm, 32 parts (0 on the bottom side), 18 nets.
